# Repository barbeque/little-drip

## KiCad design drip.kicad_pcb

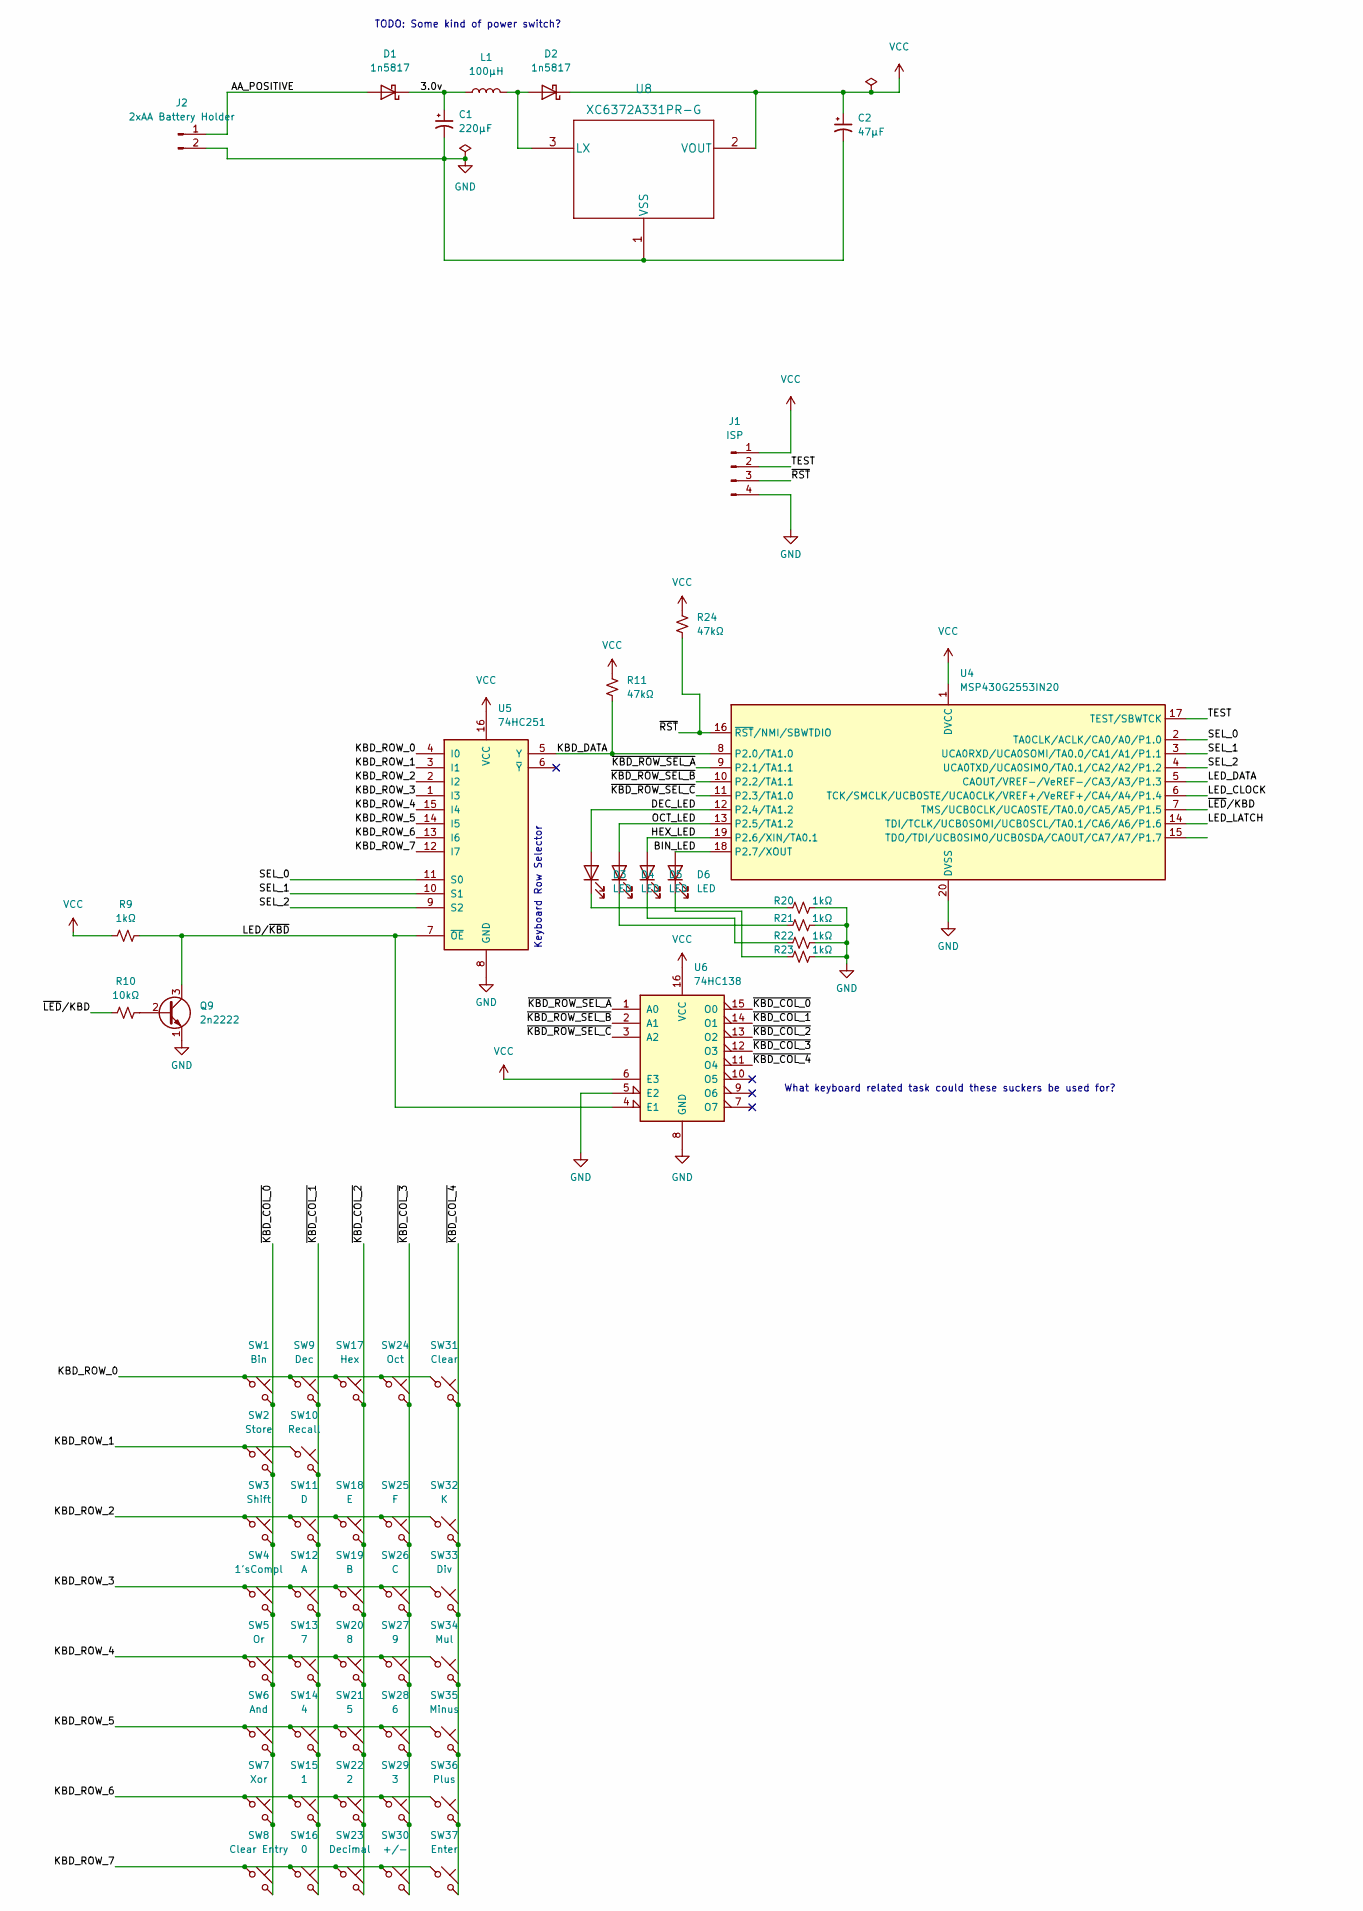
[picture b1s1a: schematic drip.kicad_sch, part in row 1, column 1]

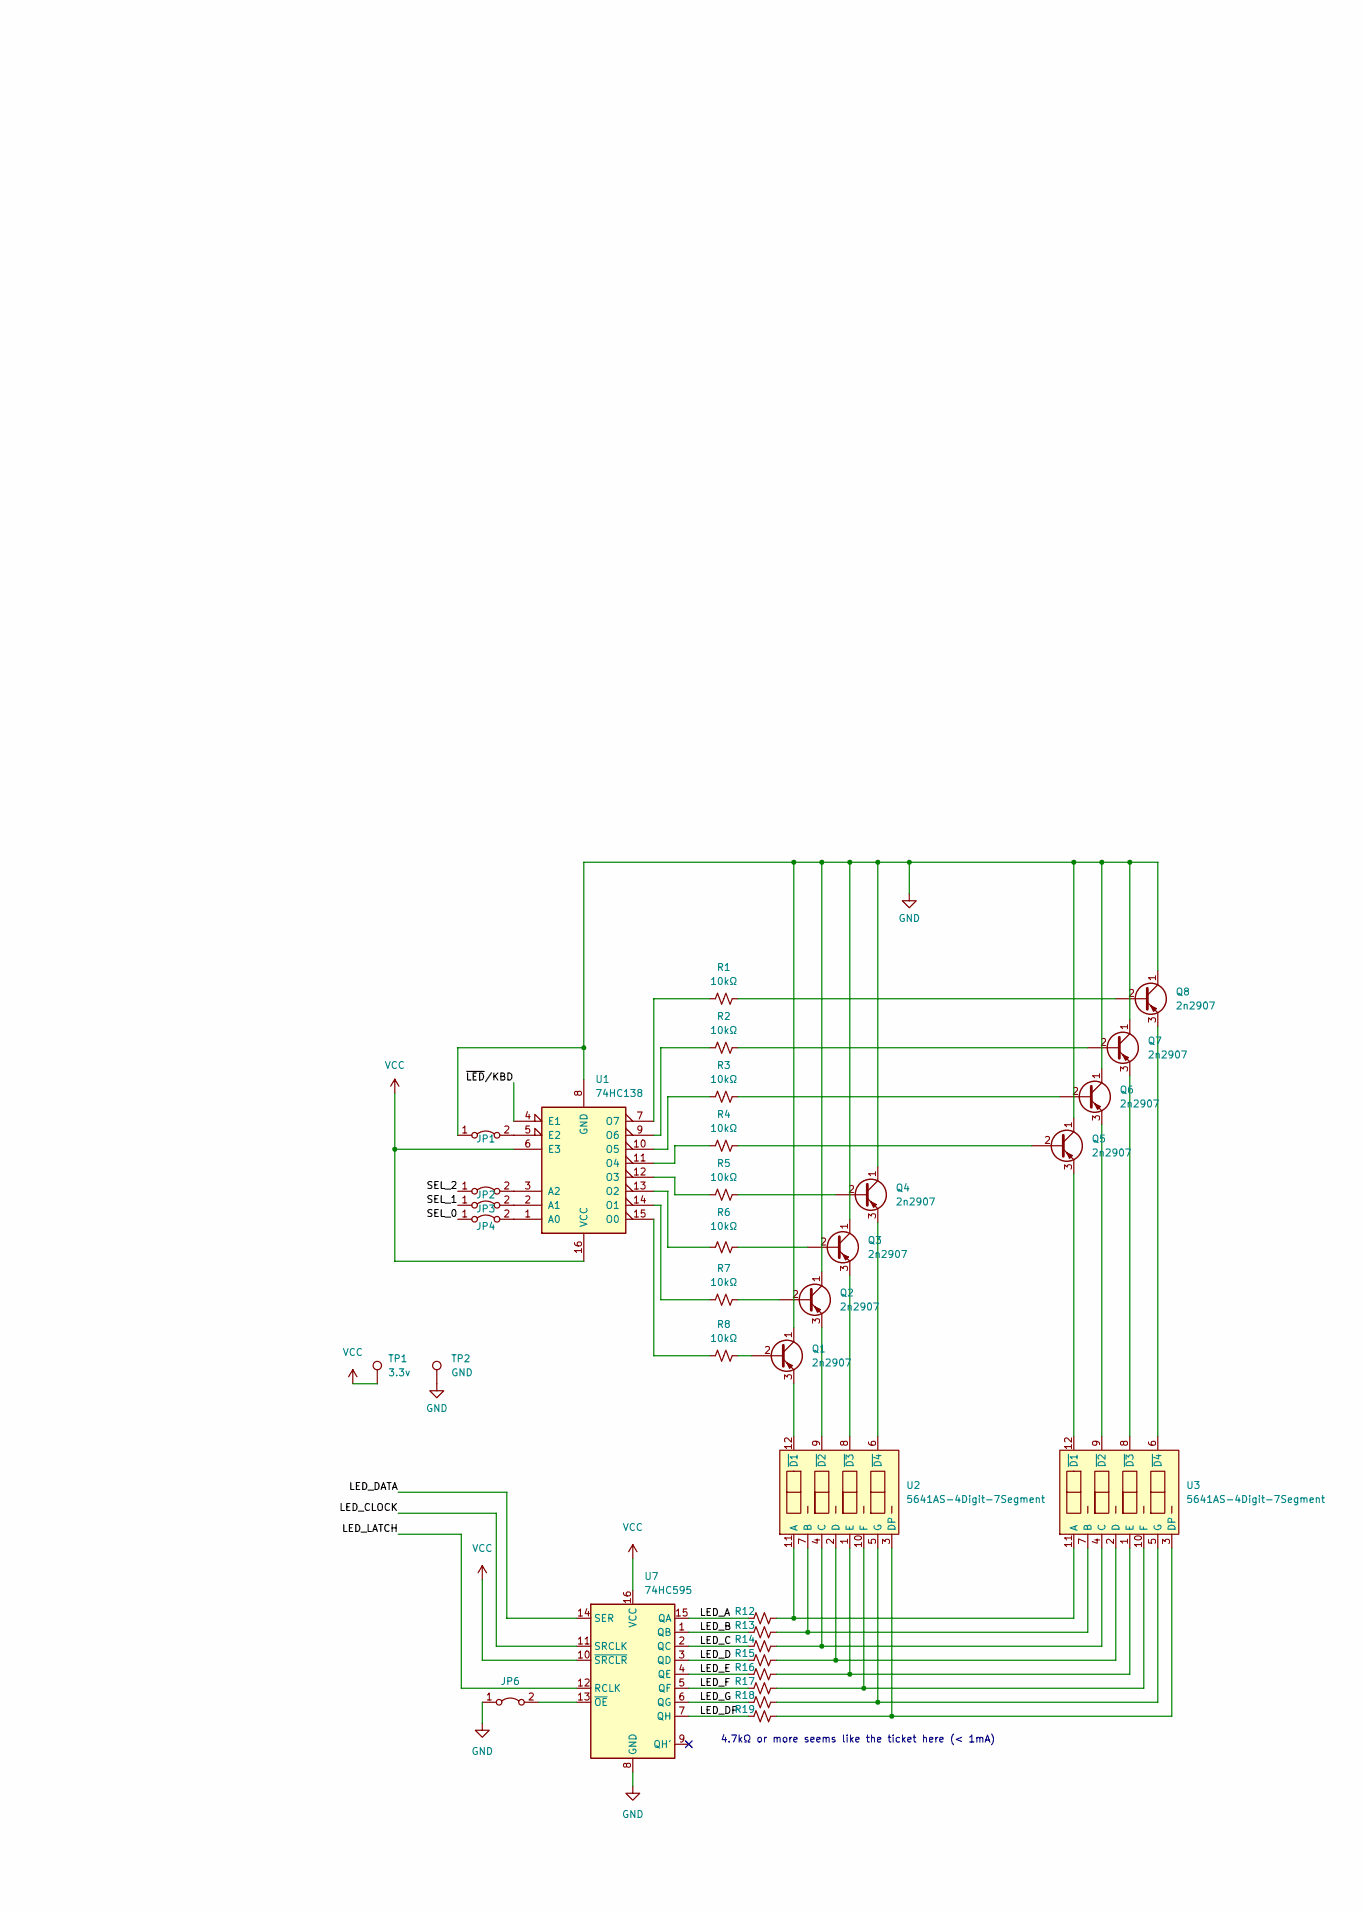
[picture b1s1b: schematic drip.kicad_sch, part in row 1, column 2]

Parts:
C1: 220µF; CP_Radial_D8.0mm_P5.00mm
C2: 47µF; CP_EIA-3528-15_AVX-H_Pad1.50x2.35mm_HandSolder; DigiKey 718-293D476X0010B2TE3TR-ND
D1, D2: 1n5817; D_DO-41_SOD81_P10.16mm_Horizontal
D3, D4, D5, D6: LED; LED_0805_2012Metric_Pad1.15x1.40mm_HandSolder
J1: ISP; PinHeader_1x04_P2.54mm_Vertical
J2: 2xAA Battery Holder; BatteryHolder_MPD_BC2AAPC_2xAA; DigiKey BC2AAPC-ND
JP1, JP2, JP3, JP4, JP6: Jumper_2_Bridged; SolderJumper-2_P1.3mm_Bridged2Bar_RoundedPad1.0x1.5mm
L1: 100µH; L_0805_2012Metric_Pad1.15x1.40mm_HandSolder
Q1, Q2, Q3, Q4, Q5, Q6, Q7, Q8: 2n2907; TO-92_Inline
Q9: 2n2222; TO-92L_Inline
R1, R2, R3, R4, R5, R6, R7, R8, R10, R12, R13, R14, R15, R16, R17, R18, R19: 10kΩ; R_Axial_DIN0207_L6.3mm_D2.5mm_P10.16mm_Horizontal
R9: 1kΩ; R_Axial_DIN0207_L6.3mm_D2.5mm_P10.16mm_Horizontal
R11, R24: 47kΩ; R_Axial_DIN0207_L6.3mm_D2.5mm_P10.16mm_Horizontal
R20, R21, R22, R23: 1kΩ; R_0805_2012Metric_Pad1.20x1.40mm_HandSolder
SW1: Bin; 8mm_G77_Push
SW2: Store; 8mm_G77_Push
SW3: Shift; 8mm_G77_Push
SW4: 1'sCompl; 8mm_G77_Push
SW5: Or; 8mm_G77_Push
SW6: And; 8mm_G77_Push
SW7: Xor; 8mm_G77_Push
SW8: Clear Entry; 8mm_G77_Push
SW9: Dec; 8mm_G77_Push
SW10: Recall; 8mm_G77_Push
SW11: D; 8mm_G77_Push
SW12: A; 8mm_G77_Push
SW13: 7; 8mm_G77_Push
SW14: 4; 8mm_G77_Push
SW15: 1; 8mm_G77_Push
SW16: 0; 8mm_G77_Push
SW17: Hex; 8mm_G77_Push
SW18: E; 8mm_G77_Push
SW19: B; 8mm_G77_Push
SW20: 8; 8mm_G77_Push
SW21: 5; 8mm_G77_Push
SW22: 2; 8mm_G77_Push
SW23: Decimal; 8mm_G77_Push
SW24: Oct; 8mm_G77_Push
SW25: F; 8mm_G77_Push
SW26: C; 8mm_G77_Push
SW27: 9; 8mm_G77_Push
SW28: 6; 8mm_G77_Push
SW29: 3; 8mm_G77_Push
SW30: +/-; 8mm_G77_Push
SW31: Clear; 8mm_G77_Push
SW32: K; 8mm_G77_Push
SW33: Div; 8mm_G77_Push
SW34: Mul; 8mm_G77_Push
SW35: Minus; 8mm_G77_Push
SW36: Plus; 8mm_G77_Push
SW37: Enter; 8mm_G77_Push
TP1: 3.3v; TestPoint_Loop_D2.50mm_Drill1.85mm
TP2: GND; TestPoint_Loop_D2.50mm_Drill1.85mm
U1, U6: 74HC138; DIP-16_W7.62mm_Socket_LongPads
U2, U3: 5641AS-4Digit-7Segment; 5641AS_THT
U4: MSP430G2553IN20; DIP-20_W7.62mm
U5: 74HC251; DIP-16_W7.62mm_Socket_LongPads
U7: 74HC595; DIP-16_W7.62mm_Socket_LongPads
U8: XC6372A331PR-G; SOT-89-3_Handsoldering

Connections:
/3.0v: C1.1, D1.1 (K), L1.1
/AA_POSITIVE: D1.2 (A), J2.1
/BIN_LED: D6.2 (A), U4.18 (P2.7/XOUT)
/DEC_LED: D3.2 (A), U4.12 (P2.4/TA1.2)
/HEX_LED: D5.2 (A), U4.19 (P2.6/XIN/TA0.1)
/KBD_DATA: R11.2, U4.8 (P2.0/TA1.0), U5.5 (Y)
/KBD_ROW_0: SW1.1, SW9.1, SW17.1, SW24.1, SW31.1, U5.4 (I0)
/KBD_ROW_1: SW2.1, SW10.1, U5.3 (I1)
/KBD_ROW_2: SW3.1, SW11.1, SW18.1, SW25.1, SW32.1, U5.2 (I2)
/KBD_ROW_3: SW4.1, SW12.1, SW19.1, SW26.1, SW33.1, U5.1 (I3)
/KBD_ROW_4: SW5.1, SW13.1, SW20.1, SW27.1, SW34.1, U5.15 (I4)
/KBD_ROW_5: SW6.1, SW14.1, SW21.1, SW28.1, SW35.1, U5.14 (I5)
/KBD_ROW_6: SW7.1, SW15.1, SW22.1, SW29.1, SW36.1, U5.13 (I6)
/KBD_ROW_7: SW8.1, SW16.1, SW23.1, SW30.1, SW37.1, U5.12 (I7)
/LED_A: R12.1, U7.15 (QA)
/LED_B: R13.1, U7.1 (QB)
/LED_C: R14.1, U7.2 (QC)
/LED_CLOCK: U4.6 (TCK/SMCLK/UCB0STE/UCA0CLK/VREF+/VeREF+/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), U7.11 (SRCLK)
/LED_D: R15.1, U7.3 (QD)
/LED_DATA: U4.5 (CAOUT/VREF-/VeREF-/CA3/A3/P1.3), U7.14 (SER)
/LED_DP: R19.1, U7.7 (QH)
/LED_E: R16.1, U7.4 (QE)
/LED_F: R17.1, U7.5 (QF)
/LED_G: R18.1, U7.6 (QG)
/LED_LATCH: U4.14 (TDI/TCLK/UCB0SOMI/UCB0SCL/TA0.1/CA6/A6/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), U7.12 (RCLK)
/LED/~KBD: Q9.3 (C), R9.2, U5.7 (~OE), U6.4 (E1)
/OCT_LED: D4.2 (A), U4.13 (P2.5/TA1.2)
/SEL_0: JP4.1 (A), U4.2 (TA0CLK/ACLK/CA0/A0/P1.0), U5.11 (S0)
/SEL_1: JP3.1 (A), U4.3 (UCA0RXD/UCA0SOMI/TA0.0/CA1/A1/P1.1), U5.10 (S1)
/SEL_2: JP2.1 (A), U4.4 (UCA0TXD/UCA0SIMO/TA0.1/CA2/A2/P1.2), U5.9 (S2)
/TEST: J1.2, U4.17 (TEST/SBWTCK)
/~KBD_COL_0: SW1.2, SW2.2, SW3.2, SW4.2, SW5.2, SW6.2, SW7.2, SW8.2, U6.15 (O0)
/~KBD_COL_1: SW9.2, SW10.2, SW11.2, SW12.2, SW13.2, SW14.2, SW15.2, SW16.2, U6.14 (O1)
/~KBD_COL_2: SW17.2, SW18.2, SW19.2, SW20.2, SW21.2, SW22.2, SW23.2, U6.13 (O2)
/~KBD_COL_3: SW24.2, SW25.2, SW26.2, SW27.2, SW28.2, SW29.2, SW30.2, U6.12 (O3)
/~KBD_COL_4: SW31.2, SW32.2, SW33.2, SW34.2, SW35.2, SW36.2, SW37.2, U6.11 (O4)
/~KBD_ROW_SEL_A: U4.9 (P2.1/TA1.1), U6.1 (A0)
/~KBD_ROW_SEL_B: U4.10 (P2.2/TA1.1), U6.2 (A1)
/~KBD_ROW_SEL_C: U4.11 (P2.3/TA1.0), U6.3 (A2)
/~LED/KBD: R10.1, U1.4 (E1), U4.7 (TMS/UCB0CLK/UCA0STE/TA0.0/CA5/A5/P1.5)
/~RST: J1.3, R24.2, U4.16 (~RST/NMI/SBWTDIO)
GND: C1.2, C2.2, J1.4, J2.2, JP1.1 (A), JP6.1 (A), Q1.1 (C), Q2.1 (C), Q3.1 (C), Q4.1 (C), Q5.1 (C), Q6.1 (C), Q7.1 (C), Q8.1 (C), Q9.1 (E), R20.2, R21.2, R22.2, R23.2, TP2.1, U1.8 (GND), U4.20 (DVSS), U5.8 (GND), U6.5 (E2), U6.8 (GND), U7.8 (GND), U8.1 (VSS)
unnamed: D2.2 (A), L1.2, U8.3 (LX)
unnamed: D3.1 (K), R20.1
unnamed: D4.1 (K), R21.1
unnamed: D5.1 (K), R22.1
unnamed: D6.1 (K), R23.1
unnamed: JP1.2 (B), U1.5 (E2)
unnamed: JP2.2 (B), U1.3 (A2)
unnamed: JP3.2 (B), U1.2 (A1)
unnamed: JP4.2 (B), U1.1 (A0)
unnamed: JP6.2 (B), U7.13 (~OE)
unnamed: Q1.2 (B), R8.2
unnamed: Q1.3 (E), U2.12 (~D1)
unnamed: Q2.2 (B), R7.2
unnamed: Q2.3 (E), U2.9 (~D2)
unnamed: Q3.2 (B), R6.2
unnamed: Q3.3 (E), U2.8 (~D3)
unnamed: Q4.2 (B), R5.2
unnamed: Q4.3 (E), U2.6 (~D4)
unnamed: Q5.2 (B), R4.2
unnamed: Q5.3 (E), U3.12 (~D1)
unnamed: Q6.2 (B), R3.2
unnamed: Q6.3 (E), U3.9 (~D2)
unnamed: Q7.2 (B), R2.2
unnamed: Q7.3 (E), U3.8 (~D3)
unnamed: Q8.2 (B), R1.2
unnamed: Q8.3 (E), U3.6 (~D4)
unnamed: Q9.2 (B), R10.2
unnamed: R1.1, U1.7 (O7)
unnamed: R2.1, U1.9 (O6)
unnamed: R3.1, U1.10 (O5)
unnamed: R4.1, U1.11 (O4)
unnamed: R5.1, U1.12 (O3)
unnamed: R6.1, U1.13 (O2)
unnamed: R7.1, U1.14 (O1)
unnamed: R8.1, U1.15 (O0)
unnamed: R12.2, U2.11 (A), U3.11 (A)
unnamed: R13.2, U2.7 (B), U3.7 (B)
unnamed: R14.2, U2.4 (C), U3.4 (C)
unnamed: R15.2, U2.2 (D), U3.2 (D)
unnamed: R16.2, U2.1 (E), U3.1 (E)
unnamed: R17.2, U2.10 (F), U3.10 (F)
unnamed: R18.2, U2.5 (G), U3.5 (G)
unnamed: R19.2, U2.3 (DP), U3.3 (DP)
VCC: C2.1, D2.1 (K), J1.1, R9.1, R11.1, R24.1, TP1.1, U1.6 (E3), U1.16 (VCC), U4.1 (DVCC), U5.16 (VCC), U6.6 (E3), U6.16 (VCC), U7.10 (~SRCLR), U7.16 (VCC), U8.2 (VOUT)

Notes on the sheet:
TODO: Some kind of power switch?
Keyboard Row Selector
4.7kΩ or more seems like the ticket here (< 1mA)
What keyboard related task could these suckers be used for?

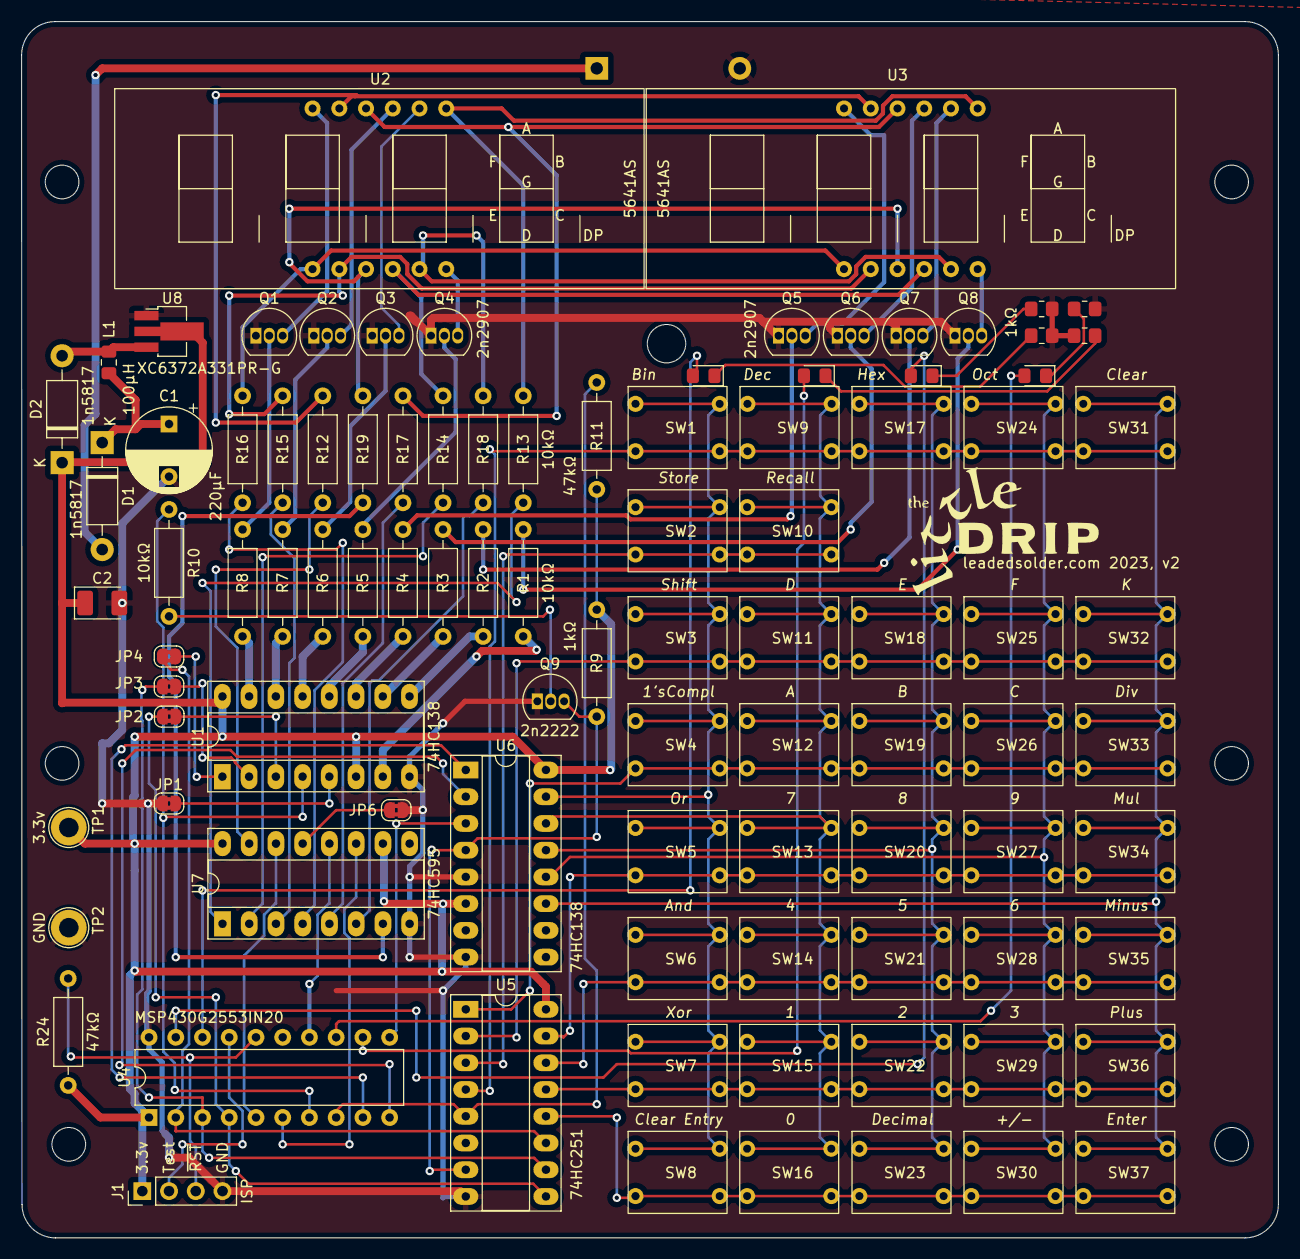
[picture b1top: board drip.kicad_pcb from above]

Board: 2 copper layers, 119.4 x 115.6 mm, 96 parts (1 on the bottom side), 86 nets.

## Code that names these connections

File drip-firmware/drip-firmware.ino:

// Pin definitions
// Selects for the 138s
#define SEL_0 P1_0 // KBD mode: column, LED mode: digit select
#define SEL_1 P1_1
#define SEL_2 P1_2
#define LED_DATA P1_3
#define LED_CLOCK P1_4
#define LED_LATCH P1_6
#define nLED_or_KBD_SEL P1_5

#define KBD_DATA P2_0
#define KBD_COL_SEL_A P2_1
#define KBD_COL_SEL_B P2_2
#define KBD_COL_SEL_C P2_3

enum LedMode {
  DEC_LED = P2_4,
  OCT_LED = P2_5,
  HEX_LED = P2_6,
  BIN_LED = P2_7
};

// TODO: Define LED 'font' and a way to clock it out
// TODO: Do a test for the letter "A" (LED A, B, C, F, E, G)

/*
 * 595 configuration:
 * QA - LED A (bit 0)
 * QB - LED B
 * QC - LED C
 * QD - LED D
 * QE - LED E
 * QF - LED F
 * QG - LED G
 * QH - LED D.P. (bit 7)
 */

enum FontSegment {
  FONT_A = 0x80,
  FONT_B = 0x40,
  FONT_C = 0x20,
  FONT_D = 0x10,
  FONT_E = 0x8,
  FONT_F = 0x4,
  FONT_G = 0x2,
  FONT_DP = 0x1
};

const unsigned char font[16] = {
  /* 0 => */ FONT_A | FONT_B | FONT_C | FONT_D | FONT_E | FONT_F,
  /* 1 => */ FONT_B | FONT_C,
  /* 2 => */ FONT_A | FONT_B | FONT_G | FONT_E | FONT_D,
  /* 3 => */ FONT_A | FONT_B | FONT_G | FONT_C | FONT_D,
  /* 4 => */ FONT_F | FONT_G | FONT_B | FONT_C,
  /* 5 => */ FONT_A | FONT_F | FONT_G | FONT_C | FONT_D,
  /* 6 => */ FONT_A | FONT_F | FONT_G | FONT_E | FONT_C | FONT_D,
  /* 7 => */ FONT_A | FONT_B | FONT_C,
  /* 8 => */ FONT_A | FONT_B | FONT_C | FONT_D | FONT_E | FONT_F | FONT_G,
  /* 9 => */ FONT_A | FONT_B | FONT_G | FONT_F | FONT_C | FONT_D,
  /* A => */ FONT_A | FONT_B | FONT_C | FONT_E | FONT_F | FONT_G,
  /* B => */ FONT_F | FONT_G | FONT_E | FONT_D | FONT_C,
  /* C => */ FONT_A | FONT_F | FONT_E | FONT_D,
  /* D => */ FONT_B | FONT_G | FONT_E | FONT_D | FONT_C,
  /* E => */ FONT_A | FONT_F | FONT_G | FONT_E | FONT_D,
  /* F => */ FONT_A | FONT_F | FONT_G | FONT_E
};

enum KeyCode {
  KEY_NIL = 0,
  KEY_0, KEY_1, KEY_2, KEY_3, KEY_4, KEY_5, KEY_6, KEY_7, KEY_8, KEY_9,
  KEY_A, KEY_B, KEY_C, KEY_D, KEY_E, KEY_F,
  KEY_BIN, KEY_DEC, KEY_HEX, KEY_OCT,
  KEY_CLEAR, KEY_STORE, KEY_RECALL, KEY_SHIFT,
  KEY_OR, KEY_AND, KEY_XOR,
  KEY_ADD, KEY_SUBTRACT, KEY_DIVIDE, KEY_MULTIPLY,
  KEY_K, KEY_1SCOMPLEMENT, KEY_DECIMAL, KEY_PLUSMINUS,
  KEY_CLEAR_ENTRY, KEY_ENTER
};

const KeyCode keyMap[8][5] = {
  { KEY_BIN, KEY_DEC, KEY_HEX, KEY_OCT, KEY_CLEAR },
  { KEY_STORE, KEY_RECALL, KEY_NIL, KEY_NIL, KEY_NIL },
  { KEY_SHIFT, KEY_D, KEY_E, KEY_F, KEY_K },
  { KEY_1SCOMPLEMENT, KEY_A, KEY_B, KEY_C, KEY_DIVIDE },
  { KEY_OR, KEY_7, KEY_8, KEY_9, KEY_MULTIPLY },
  { KEY_AND, KEY_4, KEY_5, KEY_6, KEY_SUBTRACT },
  { KEY_XOR, KEY_1, KEY_2, KEY_3, KEY_ADD },
  { KEY_CLEAR_ENTRY, KEY_0, KEY_DECIMAL, KEY_PLUSMINUS, KEY_ENTER }
};

KeyCode lastKeyPressed = KEY_NIL;

const KeyCode getKey() {
  // Must be in key-reading mode
  for(unsigned char row = 0; row < 8; ++row) {
    digitalWrite(SEL_0, row & 0x01);
    digitalWrite(SEL_1, row & 0x02);
    digitalWrite(SEL_2, row & 0x04);

    for(unsigned int col = 0; col < 5; ++col) {
      digitalWrite(KBD_COL_SEL_A, col & 0x01);
      digitalWrite(KBD_COL_SEL_B, col & 0x02);
      digitalWrite(KBD_COL_SEL_C, col & 0x04);

      // Now try to read - pretty sure this is active low
      if(!digitalRead(KBD_DATA)) {
        // TODO: Debounce?
        return keyMap[row][col];
      }
    }
  }

  return KEY_NIL; // nothing detected on this scan
}

// Note that 0 is the leftmost digit (MSB) and 7 is the rightmost (LSB)

// Calculator state
LedMode displayMode;
// TODO: Stack (how big can I make it?)
// TODO: Keyboard polling/interrupt?
// TODO: Screen refresh timer

// The current display, must be materialized into stack
// to do any operations
unsigned char display[8];
// Where the next key struck will be inserted into display buffer
unsigned char insertionPoint;

void turnOnLedDigit(unsigned char digit) {  
  // output 0: leftmost digit ($7)
  digitalWrite(SEL_0, digit & 0x01);
  digitalWrite(SEL_1, digit & 0x02);
  digitalWrite(SEL_2, digit & 0x04);
  // output 7: rightmost digit ($0)
}

/**
 * Blit a single character into a segment display
 */
void blitIntoSegmentDisplay(unsigned char character) {
  for(unsigned char i = 0; i < 8; ++i) {
    digitalWrite(LED_CLOCK, LOW);
    
    digitalWrite(LED_DATA, character & 0x01);
    
    digitalWrite(LED_CLOCK, HIGH);
    digitalWrite(LED_CLOCK, LOW);

    character = character >> 1;
  }

  // Cycle the latch so the 595 output will change
  digitalWrite(LED_LATCH, HIGH);
  digitalWrite(LED_LATCH, LOW);
}

/**
 * Update the "mode" LEDs to show what display
 * mode we are currently in (binary, hexadecimal, etc.)
 */
void updateModeLEDs() {
  digitalWrite(DEC_LED, displayMode == DEC_LED ? HIGH : LOW);
  digitalWrite(OCT_LED, displayMode == OCT_LED ? HIGH : LOW);
  digitalWrite(HEX_LED, displayMode == HEX_LED ? HIGH : LOW);
  digitalWrite(BIN_LED, displayMode == BIN_LED ? HIGH : LOW);
}

void changeDisplayMode(LedMode newMode) {
  displayMode = newMode;
  updateModeLEDs();
  // TODO: refresh display in new mode
}

void insertDigit(unsigned char digitValue) {
  display[7 - insertionPoint] = digitValue;
  insertionPoint = min(7, insertionPoint + 1);
}

// TODO: Functions to get and set the value from current entry

void setup() {
  /*Serial.begin(9600);
  Serial.write("Hello");
  
  // put your setup code here, to run once:
  pinMode(KBD_DATA, INPUT);


  pinMode(SEL_0, OUTPUT);
  pinMode(SEL_1, OUTPUT);
  pinMode(SEL_2, OUTPUT);
  pinMode(nKBD_ROW_SEL_A, OUTPUT);
  pinMode(nKBD_ROW_SEL_B, OUTPUT);
  pinMode(nKBD_ROW_SEL_C, OUTPUT);

  pinMode(LED_DATA, OUTPUT);
  pinMode(LED_CLOCK, OUTPUT);
  pinMode(nLED_or_KBD_SEL, OUTPUT);
  // place into keyboard scan mode to prevent driving the display unnecessarily
  digitalWrite(nLED_or_KBD_SEL, 1);*/

  // Mode indicator LED selection
  pinMode(DEC_LED, OUTPUT);
  pinMode(OCT_LED, OUTPUT);
  pinMode(HEX_LED, OUTPUT);
  pinMode(BIN_LED, OUTPUT);

  changeDisplayMode(DEC_LED);

  pinMode(nLED_or_KBD_SEL, OUTPUT);
  pinMode(SEL_0, OUTPUT);
  pinMode(SEL_1, OUTPUT);
  pinMode(SEL_2, OUTPUT);
  pinMode(LED_DATA, OUTPUT);
  pinMode(LED_CLOCK, OUTPUT);
  pinMode(LED_LATCH, OUTPUT);

  pinMode(KBD_DATA, INPUT);
  pinMode(KBD_COL_SEL_A, OUTPUT);
  pinMode(KBD_COL_SEL_B, OUTPUT);
  pinMode(KBD_COL_SEL_C, OUTPUT);

  digitalWrite(LED_LATCH, LOW);

  for(unsigned int i = 0; i < 8; ++i) {
    display[i] = 0;
  }
  insertionPoint = 0;

  // I am a child
  display[0] = 0x0;
  display[1] = 0xb;
  display[2] = 0x0;
  display[3] = 0x0;
  display[4] = 0xb;
  display[5] = 0x1;
  display[6] = 0xe;
  display[7] = 0x5;
}

void loop() {  
  // LED time
  digitalWrite(nLED_or_KBD_SEL, LOW);

  for(unsigned int i = 0; i < 8; ++i) {
    blitIntoSegmentDisplay(font[display[i]]);
    turnOnLedDigit(i);
  }

  // Keyboard scanning time
  digitalWrite(nLED_or_KBD_SEL, HIGH);

  KeyCode justPressed = getKey();
  
  if(justPressed != KEY_NIL && justPressed != lastKeyPressed) {
    // TODO: Pass this into another handler. For now, we'll just do something stupid
    lastKeyPressed = justPressed;
    switch(justPressed) {
      case KEY_CLEAR:
        // Wipe out the display to prove input reading works
        for(unsigned int i = 0; i < 8; ++i) {
          display[i] = 0;
          insertionPoint = 0;
        }
        break;
      case KEY_DEC:
        changeDisplayMode(DEC_LED);
        break;
      case KEY_HEX:
        changeDisplayMode(HEX_LED);
        break;
      case KEY_BIN:
        changeDisplayMode(BIN_LED);
        break;
      case KEY_OCT:
        changeDisplayMode(OCT_LED);
        break;
      case KEY_F:
        insertDigit(0xf);
        break;
      case KEY_E:
        insertDigit(0xe);
        break;
      case KEY_D:
        insertDigit(0xd);
        break;
      case KEY_C:
        insertDigit(0xc);
        break;
      case KEY_B:
        insertDigit(0xb);
        break;
      case KEY_A:
        insertDigit(0xa);
        break;
      case KEY_9:
        insertDigit(0x9);
        break;
      case KEY_8:
        insertDigit(0x8);
        break;
      case KEY_7:
        insertDigit(0x7);
        break;
      case KEY_6:
        insertDigit(0x6);
        break;
      case KEY_5:
        insertDigit(0x5);
        break;
      case KEY_4:
        insertDigit(0x4);
        break;
      case KEY_3:
        insertDigit(0x3);
        break;
      case KEY_2:
        insertDigit(0x2);
        break;
      case KEY_1:
        insertDigit(0x1);
        break;
      case KEY_0:
        insertDigit(0x0);
        break;
    } // end key switch
  } // end if key not nil

  if(justPressed == KEY_NIL) {
    // otherwise we can't press-release-press the same key
    lastKeyPressed = KEY_NIL;
  }
}

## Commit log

2023-01-03 Starting to lay out the 7Seg
2023-01-09 PNP transistors to prepare for '138 based
2023-01-09 Add a ridiculous logo
2023-01-18 Untested first draft at 5641AS 7-seg 4-digit LED
2023-01-18 '138 wired up
2023-01-25 LED driver done
2023-01-25 Reducing pins
2023-01-25 Keyboard row decode
2023-01-25 Keyboard column decode
2023-01-25 Wire the keyboard matrix properly this time
2023-01-25 Fix inverted select
2023-01-25 Use 10k on 7seg data lines
2023-01-25 Button footprint, maybe
2023-01-25 Make holes larger for 8mm
2023-01-26 Fully footprinted schematic
2023-01-26 2xAA holder
2023-01-26 Step-up converter, layout of keypad
2023-01-26 Minor PCB fettling
2023-01-26 All placed, kind of
2023-01-26 layout complete, lots of warnings
2023-01-26 Test hooks
2023-01-26 Silkscreen warnings dealt with
2023-01-27 Mode LEDs
2023-01-27 Ignore autosave poop
2023-01-31 Version 1 released to JLCPCB
2023-03-10 Begin firmware
2023-03-23 Reset pullup, move test hooks further apart
2023-03-24 7-segment working with latch bodge
2023-03-24 Post-select seems to work better
2023-03-24 Tinkering
2023-04-03 Working keyboard scanner, I think
2023-04-03 Half-busted number input
